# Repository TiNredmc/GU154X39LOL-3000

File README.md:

# GU154X39LOL-3000
GU154X39LOL-3000 PCB and BOMs.

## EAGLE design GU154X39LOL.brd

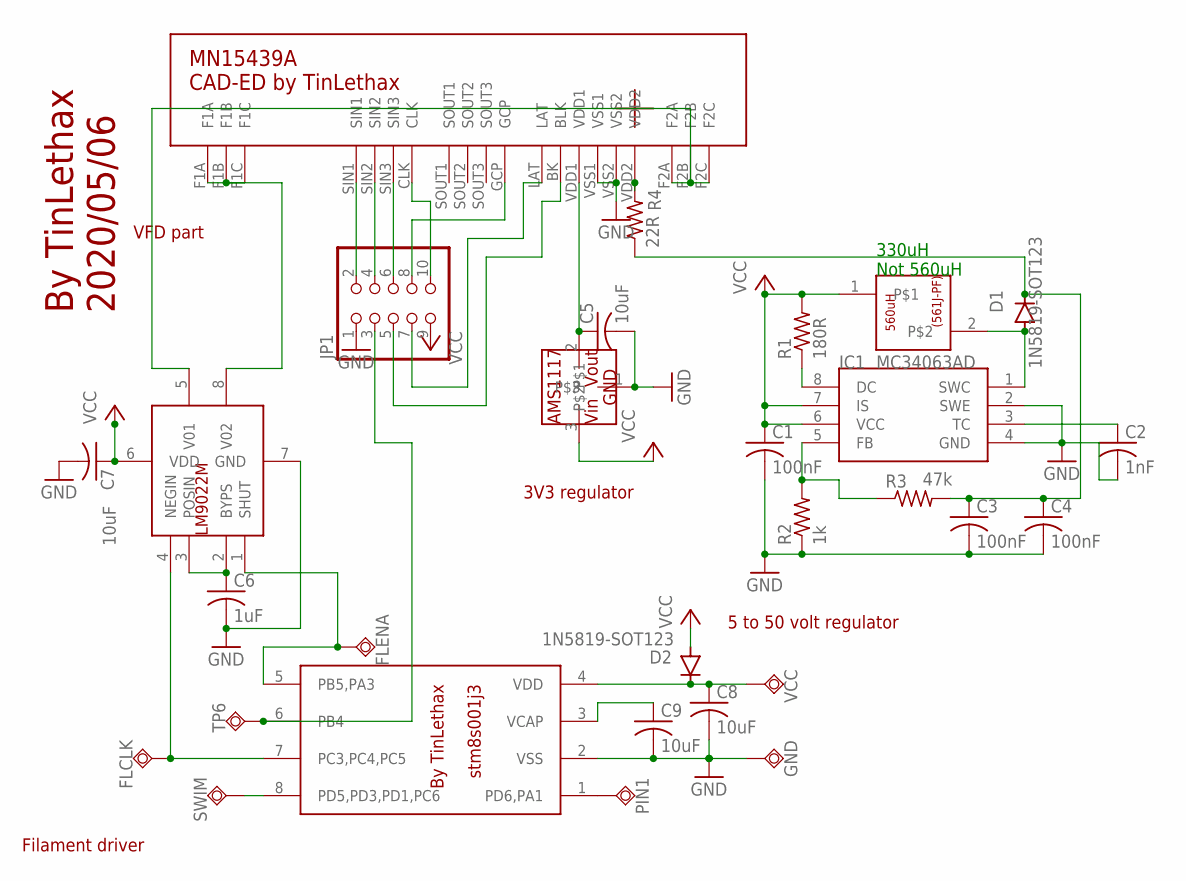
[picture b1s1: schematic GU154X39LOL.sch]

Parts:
330UH1210: 330uH; INDC4526X50N
C1, C3, C4: 100nF; C1206K
C2: 1nF; C0805
C5, C7, C8, C9: 10uF; C0805
C6: 1uF; C0805
D1, D2: 1N5819-SOT123; SOD-123_MINI-SMA
FLCLK: TPSQTP20SQ; TP20SQ
FLENA: TPSQTP20SQ; TP20SQ
GND: TPSQTP20SQ; TP20SQ
IC1: MC34063AD; SOIC8
IC2: STM8S001J3; SOP8
IC3: LM9022M; SOIC127P590X265-8N
IC4: AMS1117; SOT223
JP1: PINHD-2X5; 2X05
PIN1: TPSQTP20SQ; TP20SQ
R1: 180R; R0805
R2: 1k; R0805
R3: 47k; R0805
R4: 22R; R0805
SWIM: TPSQTP20SQ; TP20SQ
TP6: TPSQTP20SQ; TP20SQ
U$1: MN15439A; THT-20
VCC: TPSQTP20SQ; TP20SQ

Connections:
GND: C1.2, C2.2, C3.2, C4.2, C5.2, C6.2, C7.2, C8.2, C9.2, GND.TP, IC1.2 (SWE), IC1.4 (GND), IC2.2 (VSS), IC3.7 (GND), IC4.1, JP1.1, R2.1, U$1.VSS1, U$1.VSS2
unnamed: IC1.8 (DC), R1.1
unnamed: IC1.5 (FB), R2.2, R3.1
unnamed: 330UH1210.2, D1.A, IC1.1 (SWC)
unnamed: C3.1, C4.1, D1.C, R3.2, R4.1
unnamed: C2.1, IC1.3 (TC)
unnamed: C5.1, IC4.2, U$1.VDD1
unnamed: IC3.5 (V01), U$1.F2A, U$1.F2B, U$1.F2C
unnamed: IC3.8 (V02), U$1.F1A, U$1.F1B, U$1.F1C
unnamed: R4.2, U$1.VDD2
unnamed: JP1.2, U$1.SIN1
unnamed: JP1.4, U$1.SIN2
unnamed: JP1.6, U$1.SIN3
unnamed: JP1.10, U$1.CLK
unnamed: JP1.8, U$1.GCP
unnamed: JP1.7, U$1.LAT
unnamed: JP1.5, U$1.BK (BLK)
unnamed: FLCLK.TP, IC2.7 (PC3,PC4,PC5), IC3.4 (NEGIN)
unnamed: C6.1, IC3.2 (BYPS), IC3.3 (POSIN)
unnamed: FLENA.TP, IC2.5 (PB5,PA3), IC3.1 (SHUT)
unnamed: IC2.8 (PD5,PD3,PD1,PC6), SWIM.TP
unnamed: C8.1, D2.C, IC2.4 (VDD), VCC.TP
unnamed: C9.1, IC2.3 (VCAP)
unnamed: IC2.1 (PD6,PA1), PIN1.TP
unnamed: IC2.6 (PB4), JP1.3, TP6.TP
VCC: 330UH1210.1, C1.1, C7.1, D2.A, IC1.6 (VCC), IC1.7 (IS), IC3.6 (VDD), IC4.3, JP1.9, R1.2

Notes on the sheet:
330uH Not 560uH
3V3 regulator
5 to 50 volt regulator
Filament driver
VFD part
By TinLethax 2020/05/06

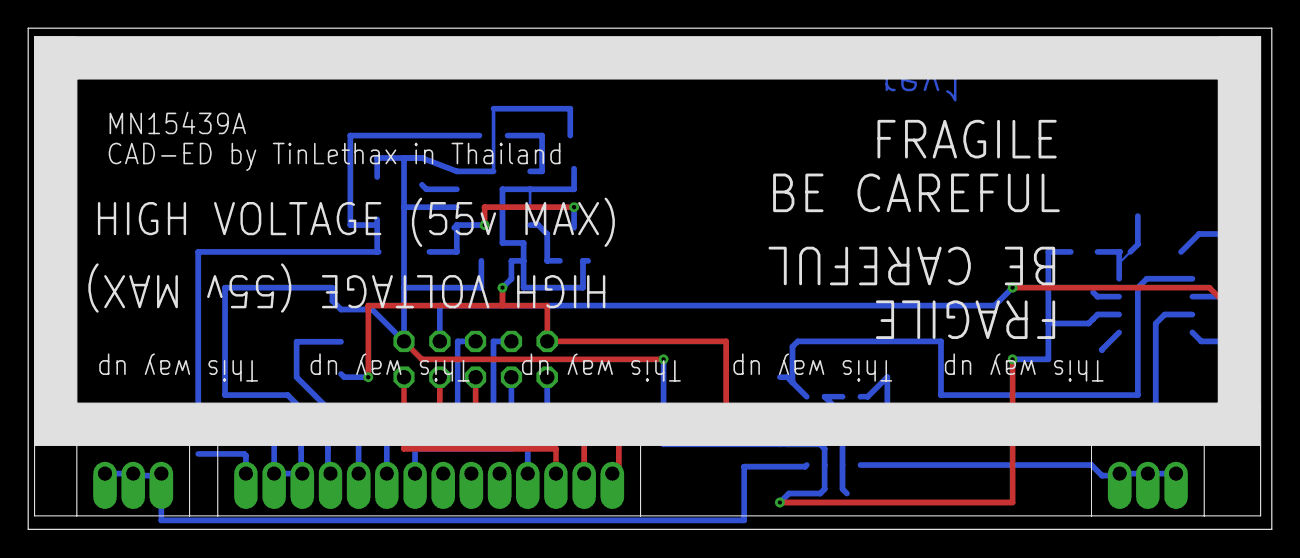
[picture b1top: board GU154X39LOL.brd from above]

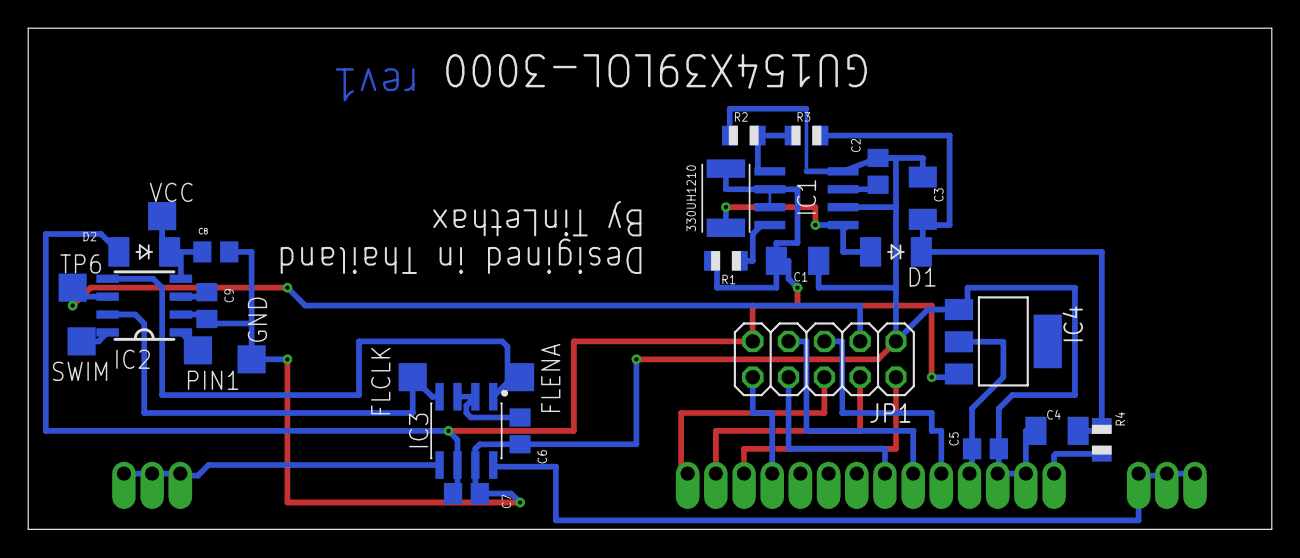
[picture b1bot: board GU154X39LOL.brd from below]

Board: 2 copper layers, 88.2 x 35.6 mm, 29 parts (28 on the bottom side), 26 nets.

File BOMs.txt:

1. x1 AMS1117 3v3 
2. x1 1nF 0603 Capacitor 16v
3. x3 100nF 1206 Capacitor 50v 
4. x1 1uF 0603 Capacitor 16v
5. x4 10uF 0605 Capacitor 16v 
6. x2 1N5819 SOT123 diode 
7. x1 2x5 Male Pin header
8. x1 330uH 1210 Inductor
9. x1 LM9022 / LM4871MX SOP-8
10. x1 MC34063AD SOP-8
11. x1 MN15439A VFD Display from Sony CDX GT700D
12. x1 180R 0805 resistor
13. x1 1K 0805 resistor
14. x1 47K 0805 resistor
15. x1 STM8S001J3 SOP-8

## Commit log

2021-08-25 Schematic and board file for MN15439A
2021-08-25 Added BOMs list
2021-08-25 Update BOMs list
